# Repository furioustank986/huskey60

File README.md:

# huskey60
Barebones hotswap 60% pcb with USB-C.
KiCad libraries can get messed up depending on what system you're on. Locate the libraries accordingly.

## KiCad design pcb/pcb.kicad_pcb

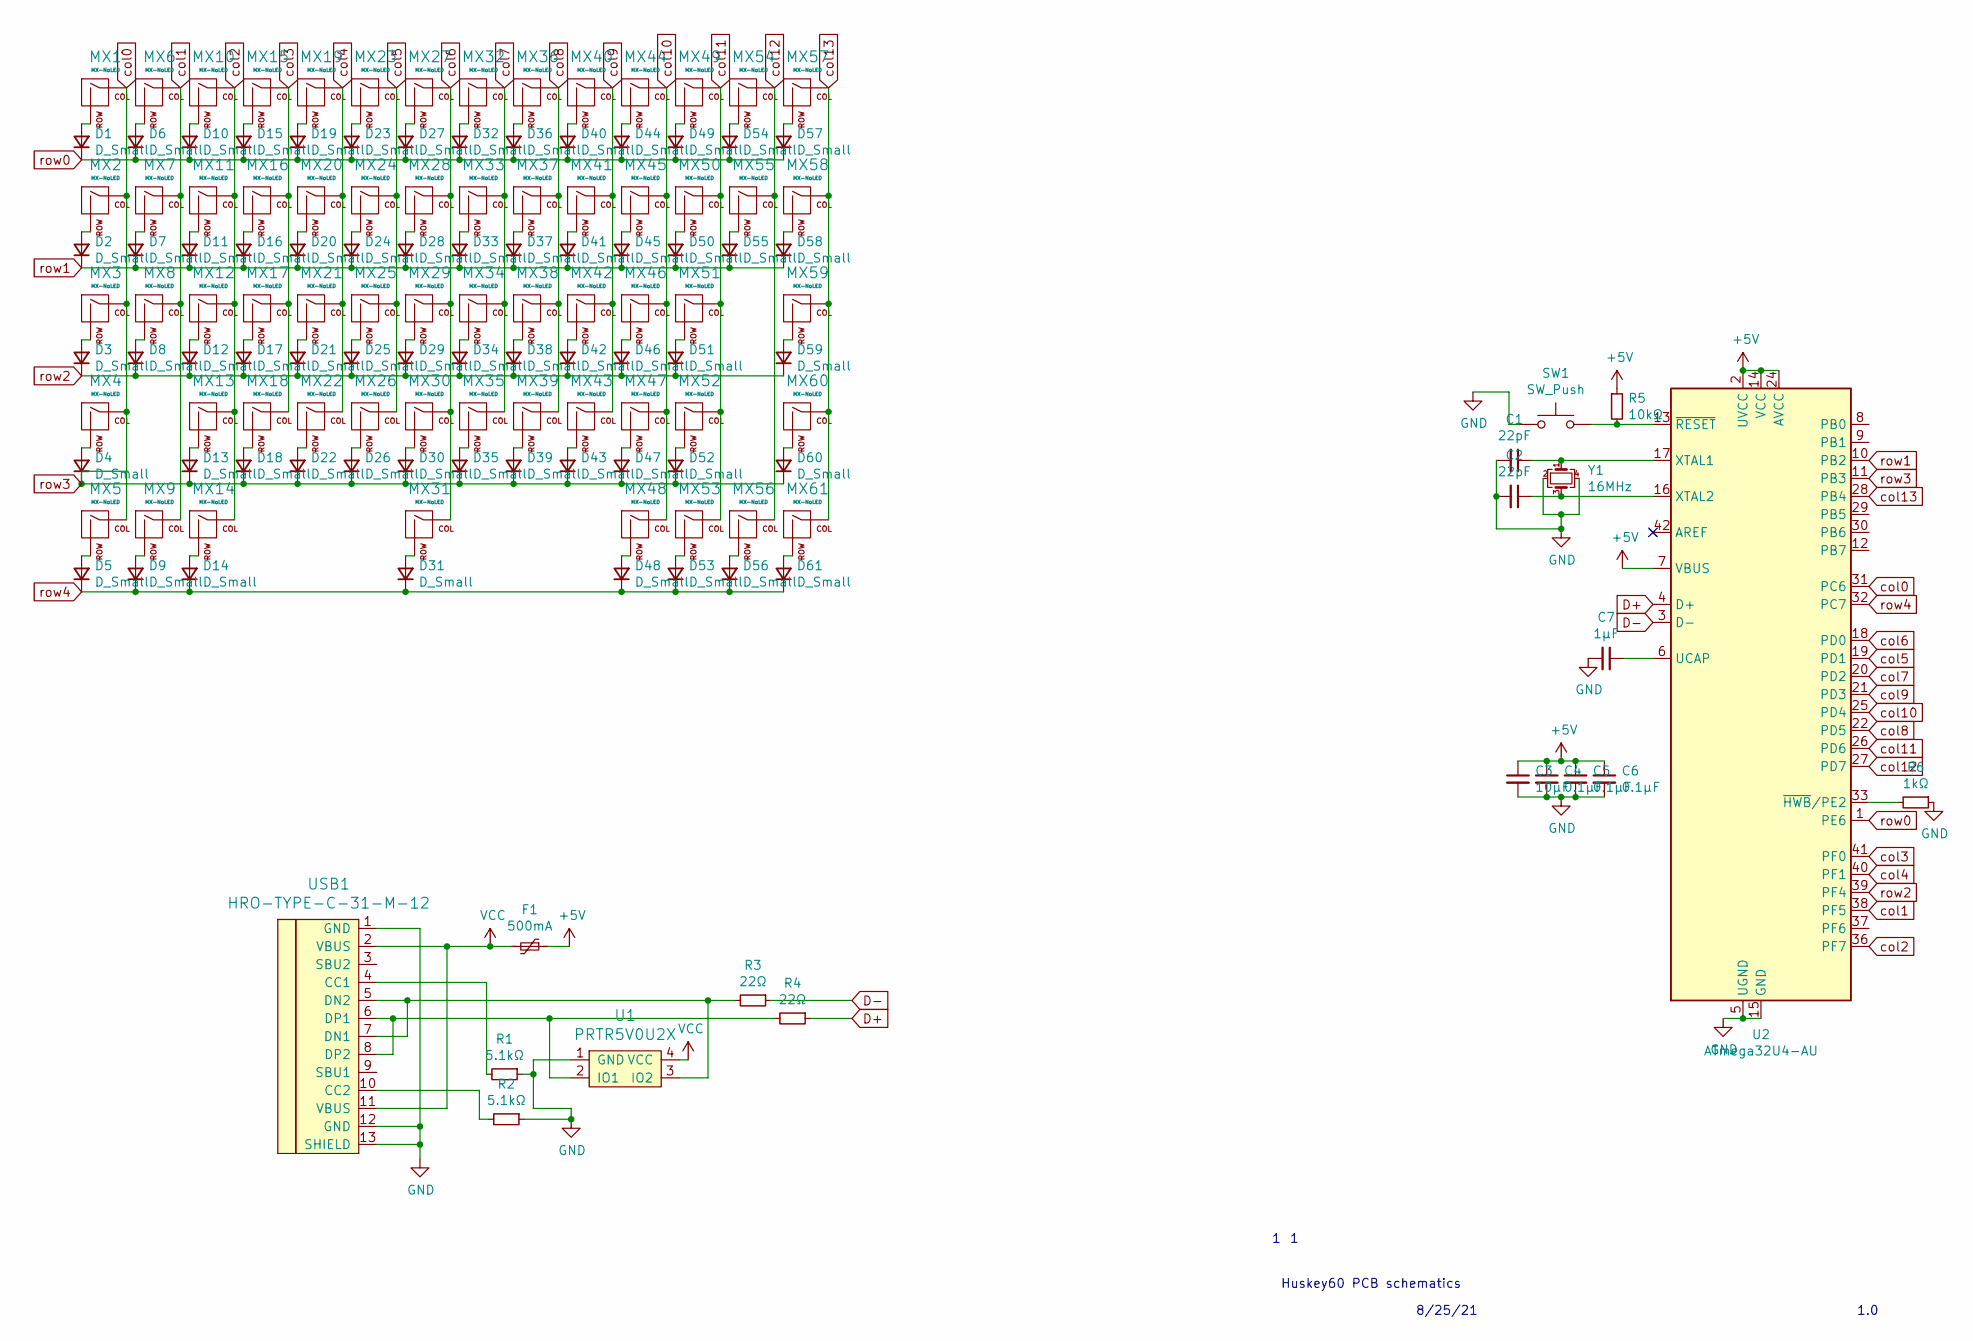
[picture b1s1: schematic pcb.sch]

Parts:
C1, C2: 22pF; C_0805_2012Metric
C3: 10µF; C_0805_2012Metric
C4, C5, C6: 0.1µF; C_0805_2012Metric
C7: 1µF; C_0805_2012Metric
D1, D2, D3, D4, D5, D6, D7, D8, D9, D10, D11, D12, D13, D14, D15, D16, D17, D18, D19, D20, D21, D22, D23, D24, D25, D26, D27, D28, D29, D30, D31, D32, D33, D34, D35, D36, D37, D38, D39, D40, D41, D42, D43, D44, D45, D46, D47, D48, D49, D50, D51, D52, D53, D54, D55, D56, D57, D58, D59, D60, D61: D_Small; D_SOD-123
F1: 500mA; Fuse_1206_3216Metric
MX1, MX6, MX7, MX8, MX10, MX11, MX12, MX13, MX15, MX16, MX17, MX18, MX19, MX20, MX21, MX22, MX23, MX24, MX25, MX26, MX27, MX28, MX29, MX30, MX32, MX33, MX34, MX35, MX36, MX37, MX38, MX39, MX40, MX41, MX42, MX43, MX44, MX45, MX46, MX47, MX49, MX50, MX51, MX52, MX54, MX55: MX-NoLED; MXOnly-1U-Hotswap
MX2, MX58: MX-NoLED; MXOnly-1.5U-Hotswap
MX3: MX-NoLED; MXOnly-1.75U-Hotswap
MX4, MX59: MX-NoLED; MXOnly-2.25U-Hotswap
MX5, MX9, MX14, MX48, MX53, MX56, MX61: MX-NoLED; MXOnly-1.25U-Hotswap
MX31: MX-NoLED; MXOnly-6.25U-Hotswap
MX57: MX-NoLED; MXOnly-2U-Hotswap
MX60: MX-NoLED; MXOnly-2.75U-Hotswap
R1, R2: 5.1kΩ; R_0805_2012Metric
R3, R4: 22Ω; R_0805_2012Metric
R5: 10kΩ; R_0805_2012Metric
R6: 1kΩ; R_0805_2012Metric
SW1: SW_Push; SKQG-1155865
U1: PRTR5V0U2X; SOT143B
U2: ATmega32U4-AU; TQFP-44_10x10mm_P0.8mm
USB1: HRO-TYPE-C-31-M-12; HRO-TYPE-C-31-M-12-Assembly
Y1: 16MHz; Crystal_SMD_3225-4Pin_3.2x2.5mm

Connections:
+5V: C3.1, C4.1, C5.1, C6.1, F1.1, R5.1, U2.2 (UVCC), U2.7 (VBUS), U2.14 (VCC), U2.24 (AVCC), U2.34 (VCC), U2.44 (AVCC)
D+: R4.1, U2.4 (D+)
D-: R3.1, U2.3 (D-)
GND: C1.2, C2.2, C3.2, C4.2, C5.2, C6.2, C7.2, R1.1, R2.1, R6.1, SW1.1, U1.1 (GND), U2.5 (UGND), U2.15 (GND), U2.23 (GND), U2.35 (GND), U2.43 (GND), USB1.1 (GND), USB1.12 (GND), USB1.13 (SHIELD), Y1.2, Y1.4
unnamed: C1.1, U2.17 (XTAL1), Y1.1
unnamed: C2.1, U2.16 (XTAL2), Y1.3
unnamed: C7.1, U2.6 (UCAP)
unnamed: D1.2 (A), MX1.2 (ROW)
unnamed: D2.2 (A), MX2.2 (ROW)
unnamed: D3.2 (A), MX3.2 (ROW)
unnamed: D4.2 (A), MX4.2 (ROW)
unnamed: D5.2 (A), MX5.2 (ROW)
unnamed: D6.2 (A), MX6.2 (ROW)
unnamed: D7.2 (A), MX7.2 (ROW)
unnamed: D8.2 (A), MX8.2 (ROW)
unnamed: D9.2 (A), MX9.2 (ROW)
unnamed: D10.2 (A), MX10.2 (ROW)
unnamed: D11.2 (A), MX11.2 (ROW)
unnamed: D12.2 (A), MX12.2 (ROW)
unnamed: D13.2 (A), MX13.2 (ROW)
unnamed: D14.2 (A), MX14.2 (ROW)
unnamed: D15.2 (A), MX15.2 (ROW)
unnamed: D16.2 (A), MX16.2 (ROW)
unnamed: D17.2 (A), MX17.2 (ROW)
unnamed: D18.2 (A), MX18.2 (ROW)
unnamed: D19.2 (A), MX19.2 (ROW)
unnamed: D20.2 (A), MX20.2 (ROW)
unnamed: D21.2 (A), MX21.2 (ROW)
unnamed: D22.2 (A), MX22.2 (ROW)
unnamed: D23.2 (A), MX23.2 (ROW)
unnamed: D24.2 (A), MX24.2 (ROW)
unnamed: D25.2 (A), MX25.2 (ROW)
unnamed: D26.2 (A), MX26.2 (ROW)
unnamed: D27.2 (A), MX27.2 (ROW)
unnamed: D28.2 (A), MX28.2 (ROW)
unnamed: D29.2 (A), MX29.2 (ROW)
unnamed: D30.2 (A), MX30.2 (ROW)
unnamed: D31.2 (A), MX31.2 (ROW)
unnamed: D32.2 (A), MX32.2 (ROW)
unnamed: D33.2 (A), MX33.2 (ROW)
unnamed: D34.2 (A), MX34.2 (ROW)
unnamed: D35.2 (A), MX35.2 (ROW)
unnamed: D36.2 (A), MX36.2 (ROW)
unnamed: D37.2 (A), MX37.2 (ROW)
unnamed: D38.2 (A), MX38.2 (ROW)
unnamed: D39.2 (A), MX39.2 (ROW)
unnamed: D40.2 (A), MX40.2 (ROW)
unnamed: D41.2 (A), MX41.2 (ROW)
unnamed: D42.2 (A), MX42.2 (ROW)
unnamed: D43.2 (A), MX43.2 (ROW)
unnamed: D44.2 (A), MX44.2 (ROW)
unnamed: D45.2 (A), MX45.2 (ROW)
unnamed: D46.2 (A), MX46.2 (ROW)
unnamed: D47.2 (A), MX47.2 (ROW)
unnamed: D48.2 (A), MX48.2 (ROW)
unnamed: D49.2 (A), MX49.2 (ROW)
unnamed: D50.2 (A), MX50.2 (ROW)
unnamed: D51.2 (A), MX51.2 (ROW)
unnamed: D52.2 (A), MX52.2 (ROW)
unnamed: D53.2 (A), MX53.2 (ROW)
unnamed: D54.2 (A), MX54.2 (ROW)
unnamed: D55.2 (A), MX55.2 (ROW)
unnamed: D56.2 (A), MX56.2 (ROW)
unnamed: D57.2 (A), MX57.2 (ROW)
unnamed: D58.2 (A), MX58.2 (ROW)
unnamed: D59.2 (A), MX59.2 (ROW)
unnamed: D60.2 (A), MX60.2 (ROW)
unnamed: D61.2 (A), MX61.2 (ROW)
unnamed: R1.2, USB1.4 (CC1)
unnamed: R2.2, USB1.10 (CC2)
unnamed: R3.2, U1.3 (IO2), USB1.5 (DN2), USB1.7 (DN1)
unnamed: R4.2, U1.2 (IO1), USB1.6 (DP1), USB1.8 (DP2)
unnamed: R5.2, SW1.2, U2.13 (~RESET)
unnamed: R6.2, U2.33 (~HWB~/PE2)
VCC: F1.2, U1.4 (VCC), USB1.2 (VBUS), USB1.11 (VBUS)
col0: MX1.1 (COL), MX2.1 (COL), MX3.1 (COL), MX4.1 (COL), MX5.1 (COL), U2.31 (PC6)
col1: MX6.1 (COL), MX7.1 (COL), MX8.1 (COL), MX9.1 (COL), U2.38 (PF5)
col2: MX10.1 (COL), MX11.1 (COL), MX12.1 (COL), MX13.1 (COL), MX14.1 (COL), U2.36 (PF7)
col3: MX15.1 (COL), MX16.1 (COL), MX17.1 (COL), MX18.1 (COL), U2.41 (PF0)
col4: MX19.1 (COL), MX20.1 (COL), MX21.1 (COL), MX22.1 (COL), U2.40 (PF1)
col5: MX23.1 (COL), MX24.1 (COL), MX25.1 (COL), MX26.1 (COL), U2.19 (PD1)
col6: MX27.1 (COL), MX28.1 (COL), MX29.1 (COL), MX30.1 (COL), MX31.1 (COL), U2.18 (PD0)
col7: MX32.1 (COL), MX33.1 (COL), MX34.1 (COL), MX35.1 (COL), U2.20 (PD2)
col8: MX36.1 (COL), MX37.1 (COL), MX38.1 (COL), MX39.1 (COL), U2.22 (PD5)
col9: MX40.1 (COL), MX41.1 (COL), MX42.1 (COL), MX43.1 (COL), U2.21 (PD3)
col10: MX44.1 (COL), MX45.1 (COL), MX46.1 (COL), MX47.1 (COL), MX48.1 (COL), U2.25 (PD4)
col11: MX49.1 (COL), MX50.1 (COL), MX51.1 (COL), MX52.1 (COL), MX53.1 (COL), U2.26 (PD6)
col12: MX54.1 (COL), MX55.1 (COL), MX56.1 (COL), U2.27 (PD7)
col13: MX57.1 (COL), MX58.1 (COL), MX59.1 (COL), MX60.1 (COL), MX61.1 (COL), U2.28 (PB4)
row0: D1.1 (K), D6.1 (K), D10.1 (K), D15.1 (K), D19.1 (K), D23.1 (K), D27.1 (K), D32.1 (K), D36.1 (K), D40.1 (K), D44.1 (K), D49.1 (K), D54.1 (K), D57.1 (K), U2.1 (PE6)
row1: D2.1 (K), D7.1 (K), D11.1 (K), D16.1 (K), D20.1 (K), D24.1 (K), D28.1 (K), D33.1 (K), D37.1 (K), D41.1 (K), D45.1 (K), D50.1 (K), D55.1 (K), D58.1 (K), U2.10 (PB2)
row2: D3.1 (K), D8.1 (K), D12.1 (K), D17.1 (K), D21.1 (K), D25.1 (K), D29.1 (K), D34.1 (K), D38.1 (K), D42.1 (K), D46.1 (K), D51.1 (K), D59.1 (K), U2.39 (PF4)
row3: D4.1 (K), D13.1 (K), D18.1 (K), D22.1 (K), D26.1 (K), D30.1 (K), D35.1 (K), D39.1 (K), D43.1 (K), D47.1 (K), D52.1 (K), D60.1 (K), U2.11 (PB3)
row4: D5.1 (K), D9.1 (K), D14.1 (K), D31.1 (K), D48.1 (K), D53.1 (K), D56.1 (K), D61.1 (K), U2.32 (PC7)

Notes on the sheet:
Huskey60 PCB schematics
8/25/21
1.0

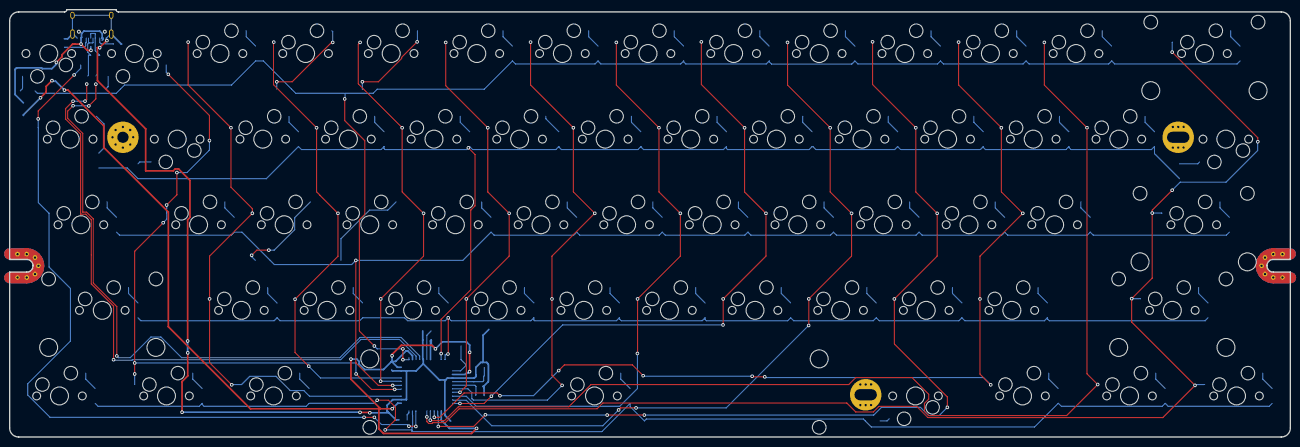
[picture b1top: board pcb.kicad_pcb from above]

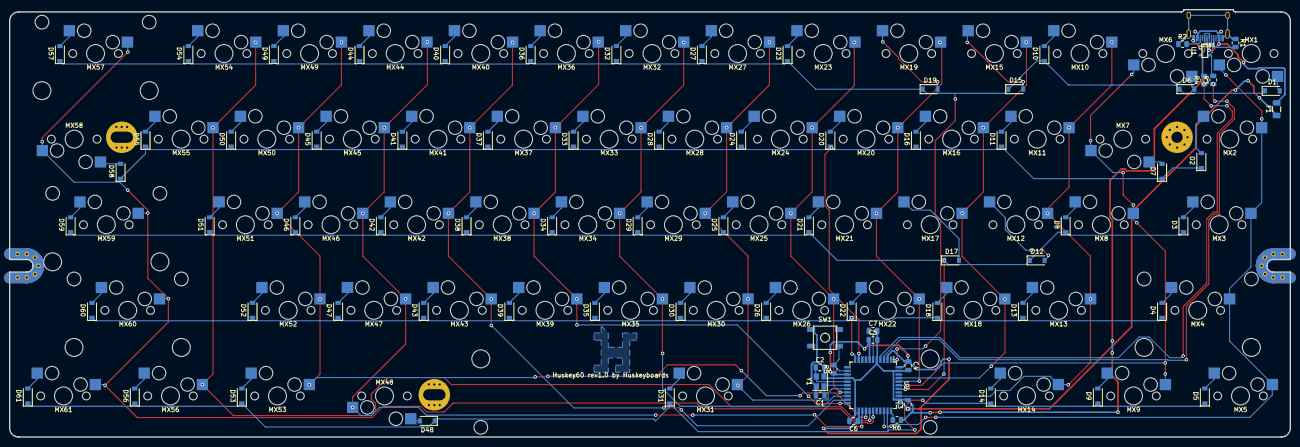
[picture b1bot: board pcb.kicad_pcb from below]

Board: 2 copper layers, 285.0 x 95.1 mm, 141 parts (80 on the bottom side), 94 nets.

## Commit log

2021-05-29 Added pcb files
2021-05-30 pcb WIP
2021-06-12 finished rev 1 PCB
2021-08-15 added locallib
2021-08-23 whatever update was done
2021-08-23 flipped spacebar stabs
2021-08-25 added new gerber files and updated pcb
2021-10-20 added gerber
